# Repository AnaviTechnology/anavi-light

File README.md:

# Anavi Light pHAT

Anavi Light pHAT is an open source hardware Raspberry Pi pHAT (add-on board) for controlling RGB LED strip powered by free and open source software. It features:

* Slot for RGB LED strip
* 12V input for the RGB LED strip
* Slot for PIR motion sensor
* Slots for up to 3 plug and play I2C sensors for temperature, barometric pressure, humidity and light
* UART (Universal asynchronous receiver/transmitter) pins for debugging
* EEPROM

# License

The project is released under the [Creative Commons Attribution-ShareAlike 4.0 International (CC BY-SA 4.0)](https://creativecommons.org/licenses/by-sa/4.0/).

Note: This is a human-readable summary of (and not a substitute for) the [license](https://creativecommons.org/licenses/by-sa/4.0/legalcode).

You are free to:

Share — copy and redistribute the material in any medium or format Adapt — remix, transform, and build upon the material for any purpose, even commercially. The licensor cannot revoke these freedoms as long as you follow the license terms. Under the following terms:

Attribution — You must give appropriate credit, provide a link to the license, and indicate if changes were made. You may do so in any reasonable manner, but not in any way that suggests the licensor endorses you or your use. ShareAlike — If you remix, transform, or build upon the material, you must distribute your contributions under the same license as the original. No additional restrictions — You may not apply legal terms or technological measures that legally restrict others from doing anything the license permits. Notices:

You do not have to comply with the license for elements of the material in the public domain or where your use is permitted by an applicable exception or limitation. No warranties are given. The license may not give you all of the permissions necessary for your intended use. For example, other rights such as publicity, privacy, or moral rights may limit how you use the material.

You will have to provide a link to the original creator of the project http://www.anavi.technology on any documentation or website.

Credit can be attributed through a link to the creator website: http://www.anavi.technology

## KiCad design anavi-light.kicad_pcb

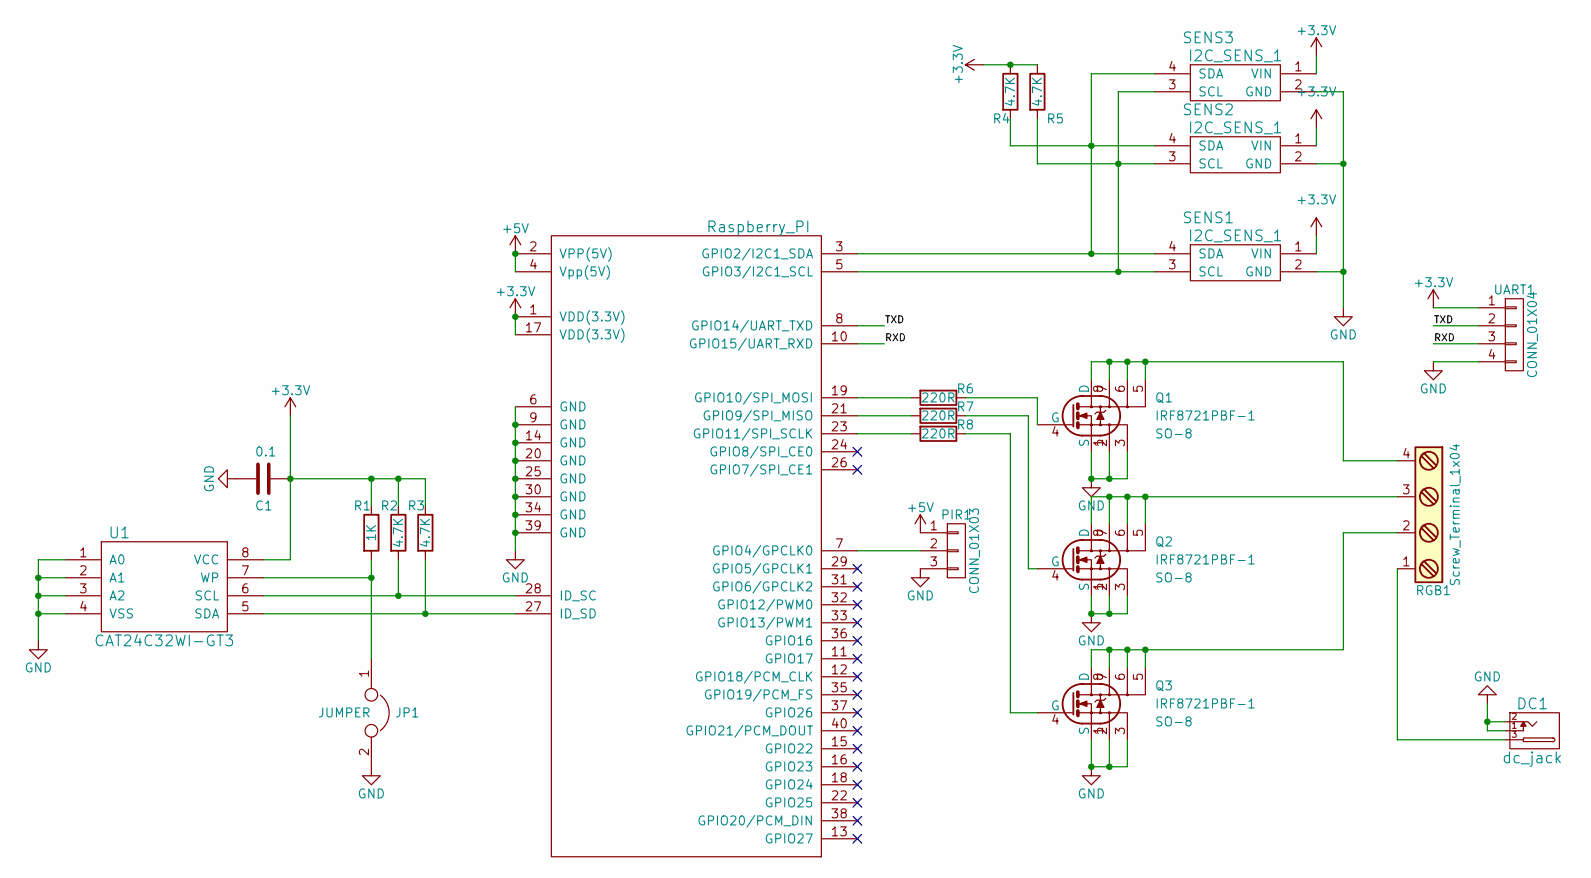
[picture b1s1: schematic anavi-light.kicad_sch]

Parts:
C1: 0.1; C_0603_HandSoldering
DC1: dc_jack; dc_socket
JP1: JUMPER; Pin_Header_Straight_1x02
PIR1: CONN_01X03; Pin_Header_Straight_1x03
Q1, Q2, Q3: IRF8721PBF-1; SO-8
R1: 1K; R_0603_HandSoldering
R2, R3, R4, R5: 4.7K; R_0603_HandSoldering
R6, R7, R8: 220R; R_0603_HandSoldering
RASP_CONN1: Raspberry_PI; Pin_Header_Straight_2x20
RGB1: Screw_Terminal_1x04; TerminalBlock_Pheonix_MKDS1.5-4pol
SENS1, SENS2, SENS3: I2C_SENS_1; Pin_Header_Straight_1x04
U1: CAT24C32WI-GT3; DIP-8_W7.62mm
UART1: CONN_01X04; Pin_Header_Straight_1x04

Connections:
+3V3: C1.1, R1.1, R2.1, R3.1, R4.1, R5.1, RASP_CONN1.1 (VDD(3.3V)), RASP_CONN1.17 (VDD(3.3V)), SENS1.1 (VIN), SENS2.1 (VIN), SENS3.1 (VIN), U1.8 (VCC), UART1.1; also elsewhere on the board
+5V: PIR1.1, RASP_CONN1.2 (VPP(5V)), RASP_CONN1.4 (Vpp(5V)); also elsewhere on the board
/RXD: RASP_CONN1.10 (GPIO15/UART_RXD), UART1.3; also elsewhere on the board
/TXD: RASP_CONN1.8 (GPIO14/UART_TXD), UART1.2; also elsewhere on the board
GND: C1.2, DC1.1, DC1.2, JP1.2, PIR1.3, Q1.1 (S), Q1.2, Q1.3, Q2.1 (S), Q2.2, Q2.3, Q3.1 (S), Q3.2, Q3.3, RASP_CONN1.6 (GND), RASP_CONN1.9 (GND), RASP_CONN1.14 (GND), RASP_CONN1.20 (GND), RASP_CONN1.25 (GND), RASP_CONN1.30 (GND), RASP_CONN1.34 (GND), RASP_CONN1.39 (GND), SENS1.2 (GND), SENS2.2 (GND), SENS3.2 (GND), U1.1 (A0), U1.2 (A1), U1.3 (A2), U1.4 (VSS), UART1.4; also elsewhere on the board
unnamed: DC1.3, RGB1.1
unnamed: JP1.1, R1.2, U1.7 (WP)
unnamed 7: PIR1.2, RASP_CONN1.7 (GPIO4/GPCLK0); also elsewhere on the board
unnamed: Q1.4 (G), R6.1
unnamed: Q1.5, Q1.6, Q1.7, Q1.8 (D), RGB1.4
unnamed: Q2.4 (G), R7.1
unnamed: Q2.5, Q2.6, Q2.7, Q2.8 (D), RGB1.3
unnamed: Q3.4 (G), R8.1
unnamed: Q3.5, Q3.6, Q3.7, Q3.8 (D), RGB1.2
unnamed: R2.2, RASP_CONN1.28 (ID_SC), U1.6 (SCL)
unnamed: R3.2, RASP_CONN1.27 (ID_SD), U1.5 (SDA)
unnamed: R4.2, RASP_CONN1.3 (GPIO2/I2C1_SDA), SENS1.4 (SDA), SENS2.4 (SDA), SENS3.4 (SDA)
unnamed: R5.2, RASP_CONN1.5 (GPIO3/I2C1_SCL), SENS1.3 (SCL), SENS2.3 (SCL), SENS3.3 (SCL)
unnamed: R6.2, RASP_CONN1.19 (GPIO10/SPI_MOSI)
unnamed: R7.2, RASP_CONN1.21 (GPIO9/SPI_MISO)
unnamed: R8.2, RASP_CONN1.23 (GPIO11/SPI_SCLK)

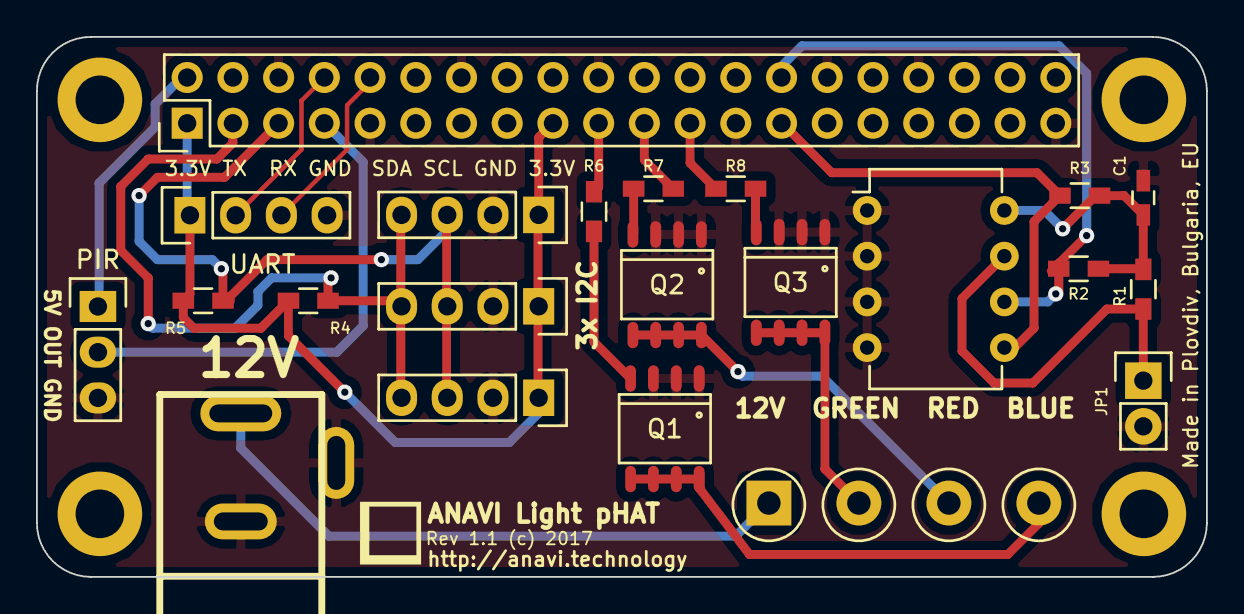
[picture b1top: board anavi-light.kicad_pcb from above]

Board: 2 copper layers, 65.0 x 30.0 mm, 26 parts (0 on the bottom side), 21 nets.

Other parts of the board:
PIR: CONN_01X03; Pin_Header_Straight_1x03
REF1, REF2, REF3, REF4: MountingHole_2.7mm_M2.5_DIN965_Pad
UART: CONN_01X04; Pin_Header_Straight_1x04

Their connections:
+3V3: UART.1; also elsewhere on the board
+5V: PIR.1; also elsewhere on the board
/RXD: UART.3; also elsewhere on the board
/TXD: UART.2; also elsewhere on the board
GND: PIR.3, UART.4; also elsewhere on the board
unnamed 7: PIR.2; also elsewhere on the board

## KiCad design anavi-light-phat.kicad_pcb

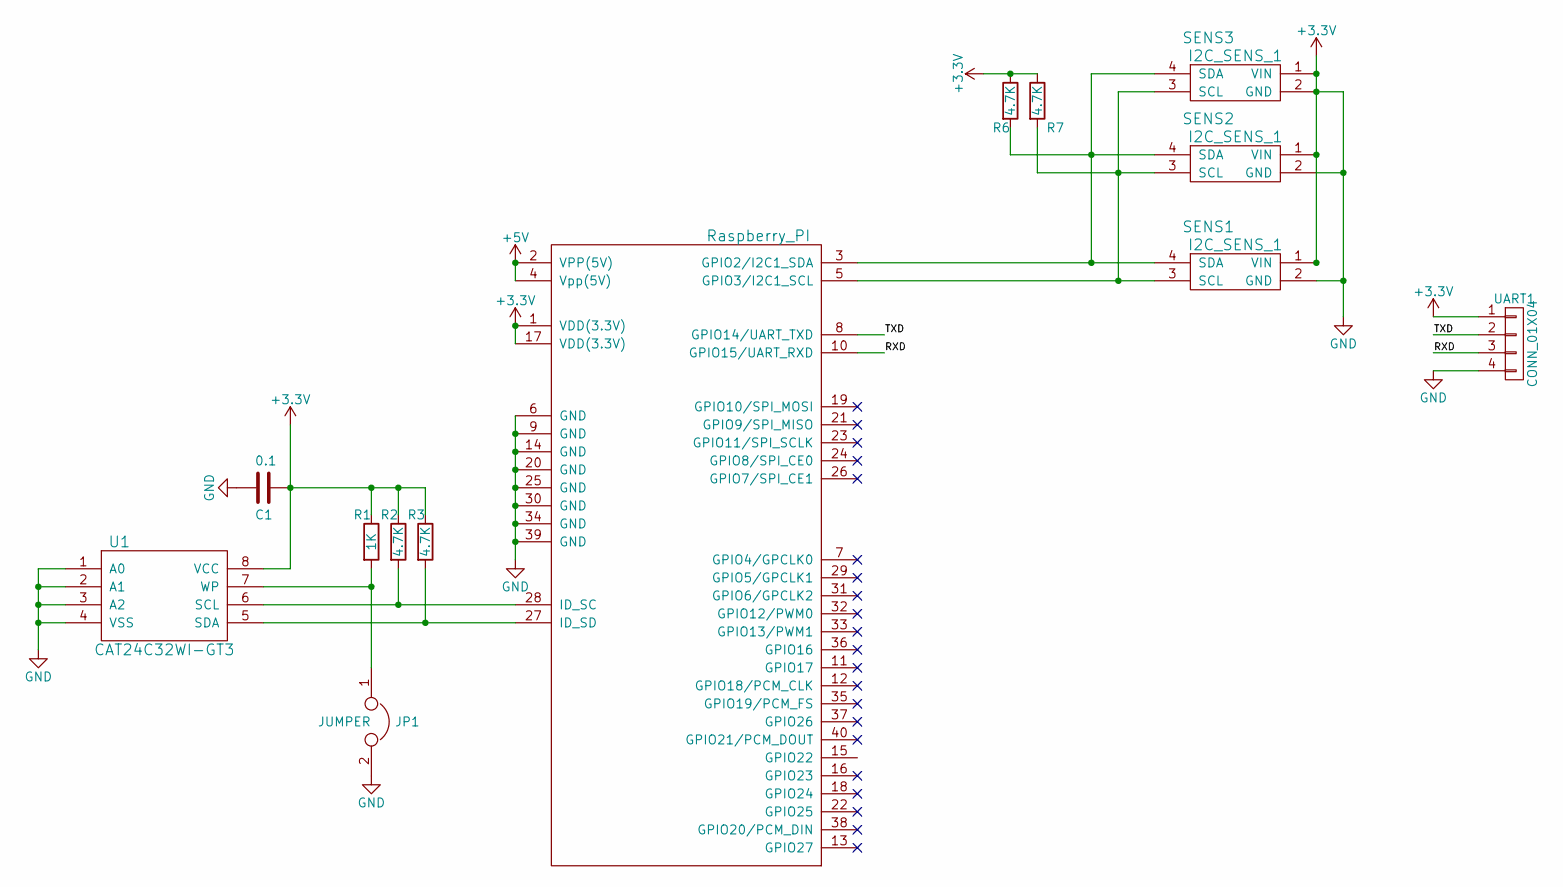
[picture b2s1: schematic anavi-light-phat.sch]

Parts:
C1: 0.1; C_0603_HandSoldering
JP1: JUMPER; Pin_Header_Straight_1x02
R1: 1K; R_0603_HandSoldering
R2, R3, R6, R7: 4.7K; R_0603_HandSoldering
RASP_CONN1: Raspberry_PI; Pin_Header_Straight_2x20
SENS1, SENS2, SENS3: I2C_SENS_1; Pin_Header_Straight_1x04
U1: CAT24C32WI-GT3; DIP-8_W7.62mm
UART1: CONN_01X04; Pin_Header_Straight_1x04

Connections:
+3V3: C1.1, C1.2, JP1.2, R1.1, R2.1, R3.1, R6.1, R7.1, RASP_CONN1.1 (VDD(3.3V)), RASP_CONN1.6 (GND), RASP_CONN1.9 (GND), RASP_CONN1.14 (GND), RASP_CONN1.17 (VDD(3.3V)), RASP_CONN1.20 (GND), RASP_CONN1.25 (GND), RASP_CONN1.30 (GND), RASP_CONN1.34 (GND), RASP_CONN1.39 (GND), SENS1.1 (VIN), SENS1.2 (GND), SENS2.1 (VIN), SENS2.2 (GND), SENS3.1 (VIN), SENS3.2 (GND), U1.1 (A0), U1.2 (A1), U1.3 (A2), U1.4 (VSS), U1.8 (VCC), UART1.1, UART1.4
+5V: RASP_CONN1.2 (VPP(5V)), RASP_CONN1.4 (Vpp(5V))
/RXD: RASP_CONN1.10 (GPIO15/UART_RXD), UART1.3
/TXD: RASP_CONN1.8 (GPIO14/UART_TXD), UART1.2
unnamed: JP1.1, R1.2, U1.7 (WP)
unnamed: R2.2, RASP_CONN1.28 (ID_SC), U1.6 (SCL)
unnamed: R3.2, RASP_CONN1.27 (ID_SD), U1.5 (SDA)
unnamed: R6.2, RASP_CONN1.3 (GPIO2/I2C1_SDA), SENS1.4 (SDA), SENS2.4 (SDA), SENS3.4 (SDA)
unnamed: R7.2, RASP_CONN1.5 (GPIO3/I2C1_SCL), SENS1.3 (SCL), SENS2.3 (SCL), SENS3.3 (SCL)

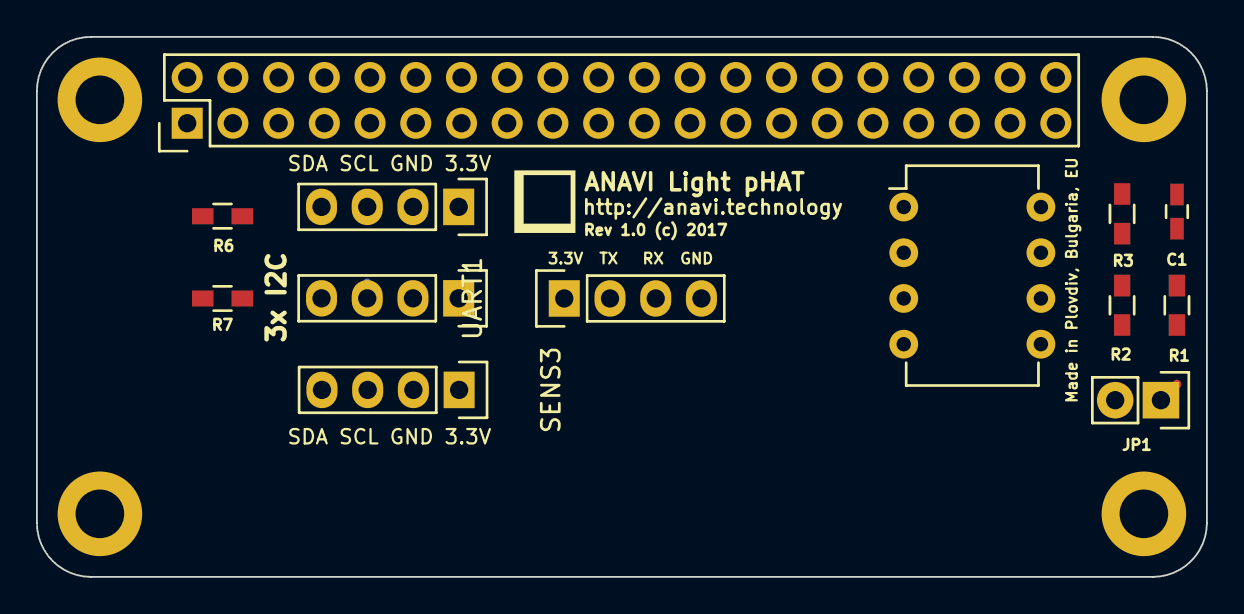
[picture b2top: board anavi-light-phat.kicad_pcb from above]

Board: 2 copper layers, 65.0 x 30.0 mm, 17 parts (0 on the bottom side), 9 nets.

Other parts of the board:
REF1, REF2, REF3, REF4: MountingHole_2.7mm_M2.5_DIN965_Pad

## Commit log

2017-07-17 ANAVI Light pHAT: Create KiCAD project
2017-07-17 Add basic schematics
2017-07-18 ANAVI Light pHAT revision 1.0
2017-07-19 anavi-light: Fixes
    Suggested-by: Rangel Ivanov <rangelivanov88@gmail.com>
2017-07-20 Adjust labels on front silkscreen
2017-07-20 anavi-light.kicad_pcb: Improve routing
2017-08-14 Add MOSFET gate resistors
2017-08-14 anavi-light.kicad_pcb: revision 1.1
2017-12-08 README.md: CC BY-SA 4.0
    Switch license to CC BY-SA 4.0 to comply with
    the requirements for open source hardware.
2023-04-12 anavi-light: Port to KiCad 6
    Port project to KiCad 6.

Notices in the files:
anavi-light-phat.kicad_pcb:
Rev 1.0 (c) 2017
anavi-light.kicad_pcb:
Rev 1.1 (c) 2017
